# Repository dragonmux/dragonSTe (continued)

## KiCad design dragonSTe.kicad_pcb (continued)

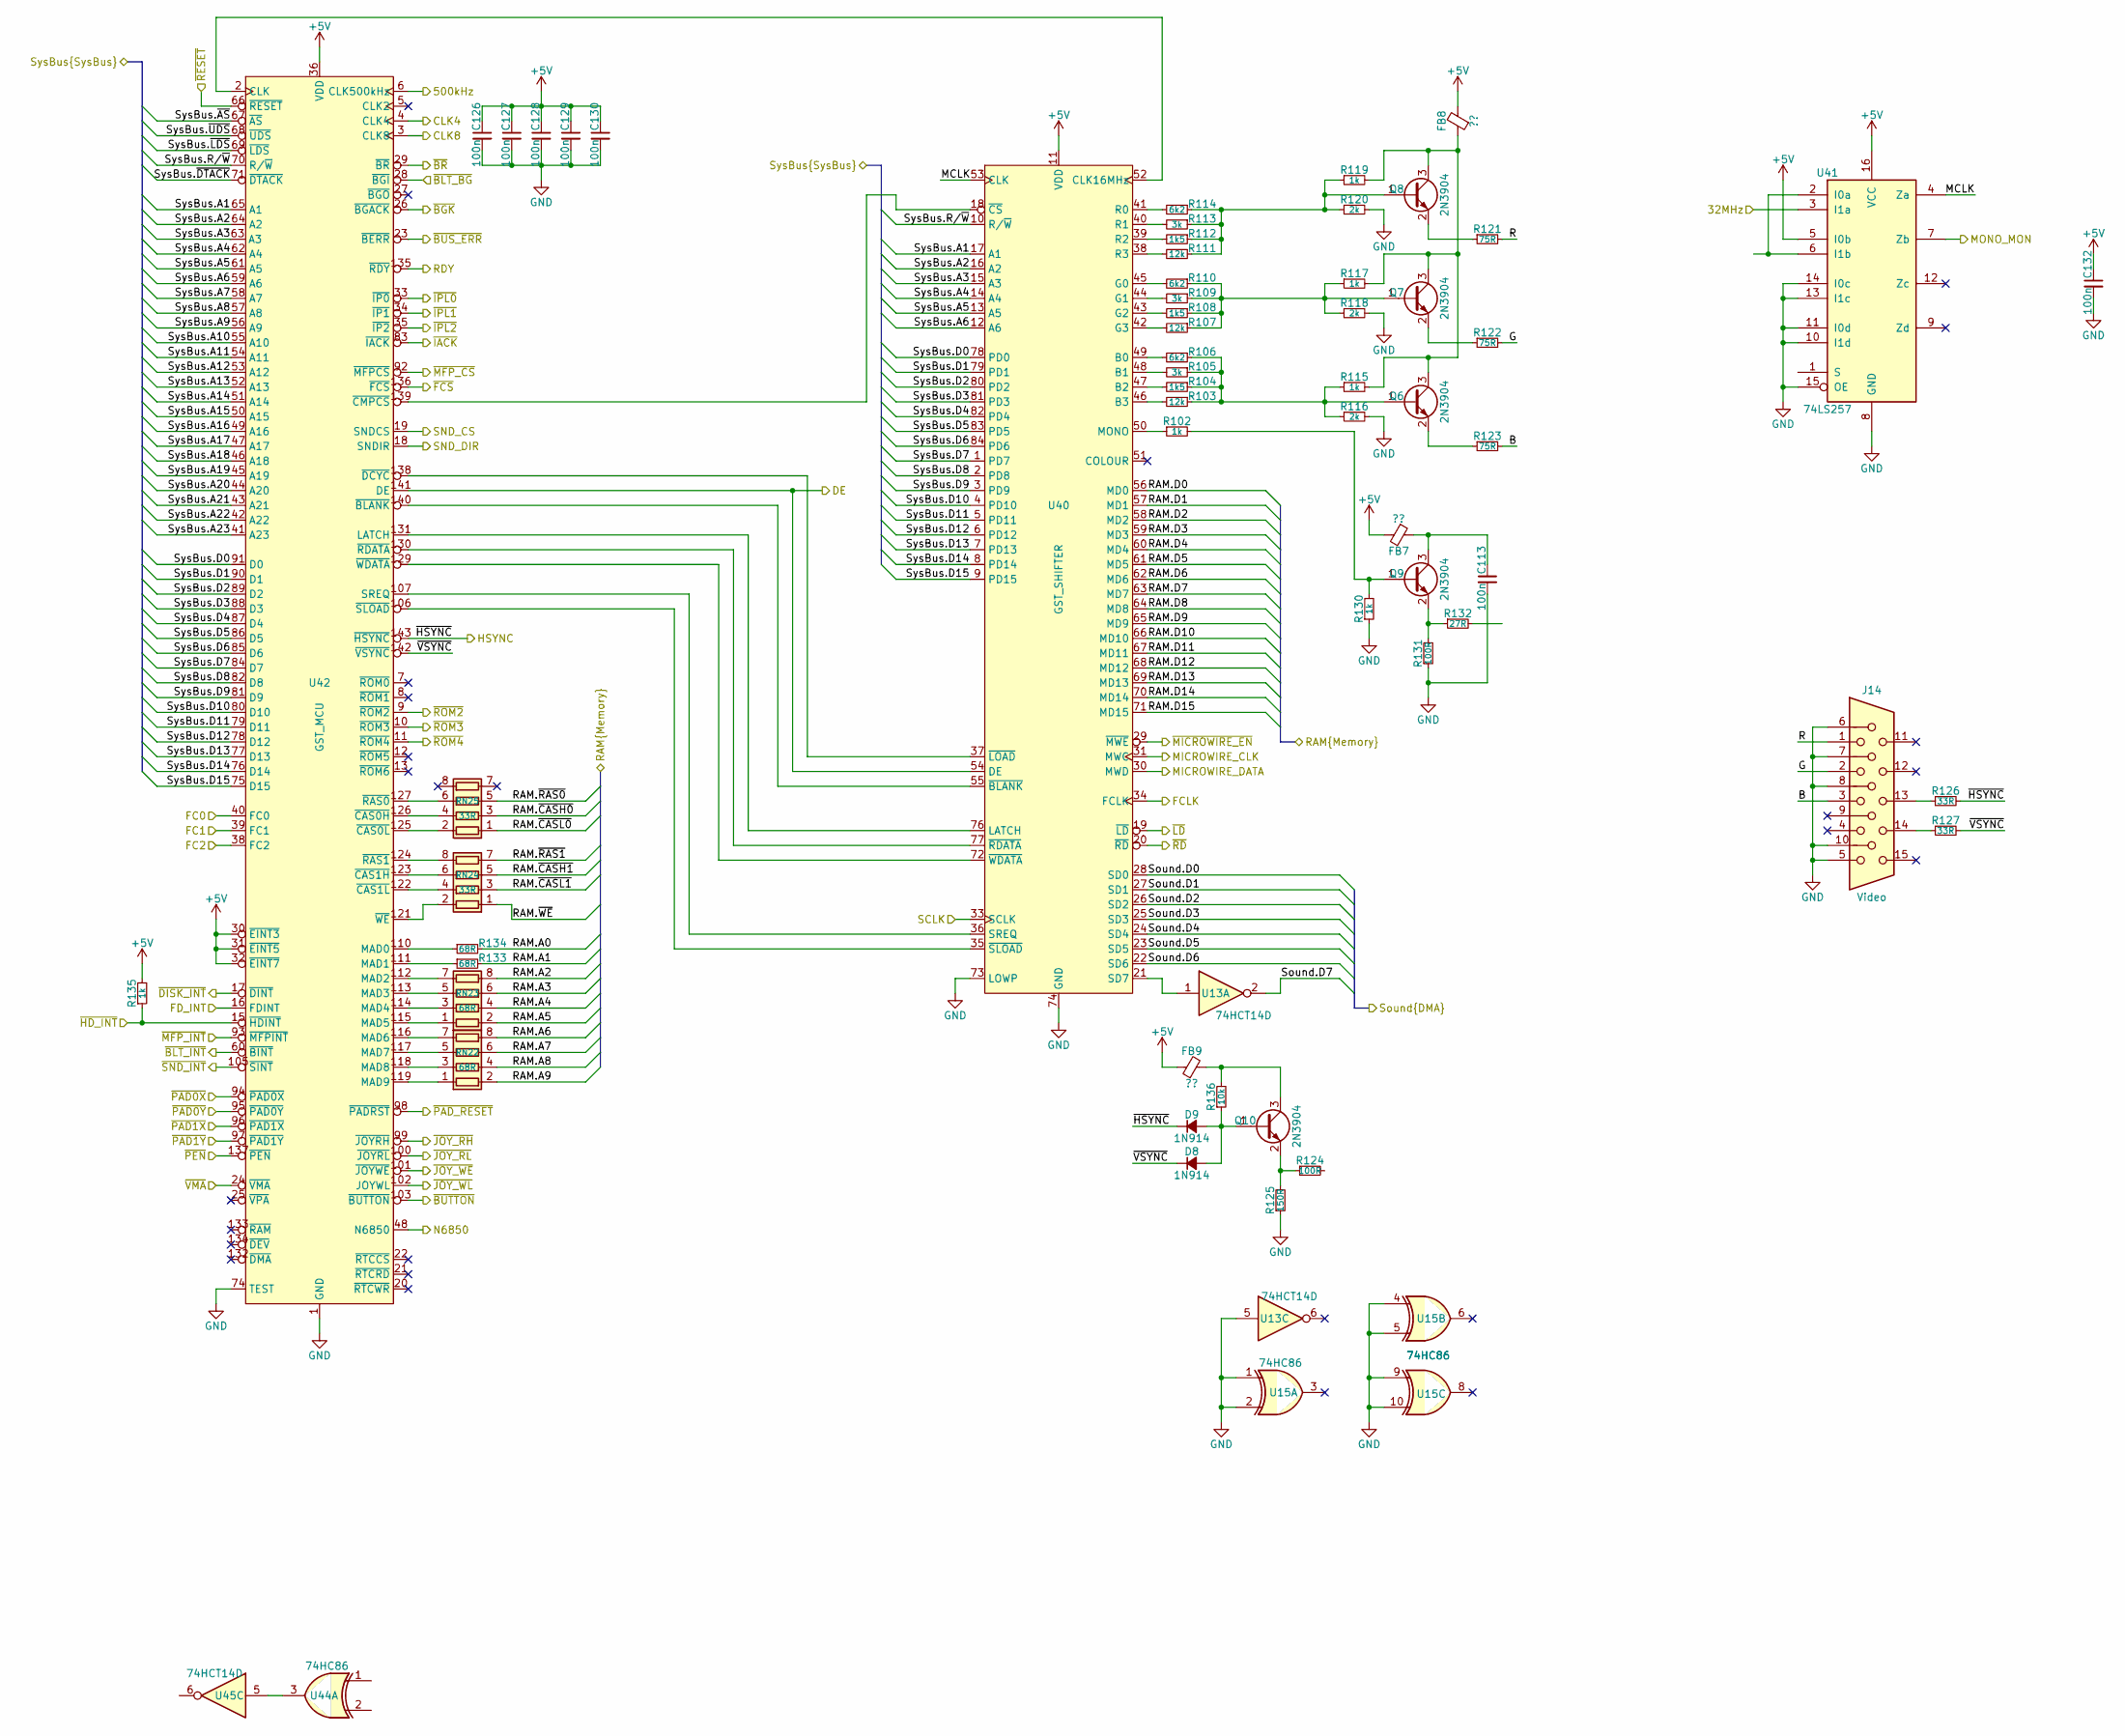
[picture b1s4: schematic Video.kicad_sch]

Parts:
C113, C126, C127, C128, C129, C130, C132: 100n; C0603
D8, D9: 1N914; D_SOD-323F; MPN 1N914BWS
FB7, FB8, FB9: ??
J14: Video; DSUB-15-HD_Socket_Horizontal_P2.29x2.54mm_EdgePinOffset8.35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
Q6, Q7, Q8, Q9, Q10: 2N3904; SOT-23; MPN MMBT3904,215
R102, R115, R117, R119, R130, R135: 1k; R0603
R103, R107, R111: 12k; R0603
R104, R108, R112: 1k5; R0603
R105, R109, R113: 3k; R0603
R106, R110, R114: 6k2; R0603
R116, R118, R120: 2k; R0603
R121, R122, R123: 75R; R0603
R124, R131: 100R; R0603
R125: 150R; R0603
R126, R127: 33R; R0603
R132: 27R; R0603
R133, R134: 68R; R0402
R136: 10k; R0603
RN22, RN23: 68R; R0402_Array_Convex_4
RN24, RN25: 33R; R0402_Array_Convex_4
U13, U45: 74HCT14D; SO-14_3.9x8.65mm_P1.27mm; MPN 74HCT14D,653
U15, U44: 74HC86; SO-14_3.9x8.65mm_P1.27mm; MPN 74HC86D,653
U40: GST_SHIFTER; PLCC-84_SMD-Socket
U41: 74LS257; TSSOP-16_4.4x5mm_P0.65mm; MPN 74HC257PW,118
U42: GST_MCU; LQFP-144_20x20mm_P0.5mm

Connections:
+5V: C126.1, C127.1, C128.1, C129.1, C130.1, C132.1, FB7.2, FB8.2, FB9.1, R135.2, U40.11 (VDD), U40.32 (VDD), U41.5 (I0b), U41.16 (VCC), U42.30 (~EINT3), U42.31 (~EINT5), U42.32 (~EINT7), U42.36 (VDD), U42.72 (VDD), U42.108 (VDD), U42.120 (VDD), U42.144 (VDD); also elsewhere on the board
/CPU+ROMs/32MHz: U41.3 (I1a); also elsewhere on the board
/CPU+ROMs/CLK8: U42.3 (CLK8); also elsewhere on the board
/CPU+ROMs/FC0: U42.40 (FC0); also elsewhere on the board
/CPU+ROMs/FC1: U42.39 (FC1); also elsewhere on the board
/CPU+ROMs/FC2: U42.38 (FC2); also elsewhere on the board
/CPU+ROMs/SysBus.A1: U40.17 (A1), U42.65 (A1); also elsewhere on the board
/CPU+ROMs/SysBus.A2: U40.16 (A2), U42.64 (A2); also elsewhere on the board
/CPU+ROMs/SysBus.A3: U40.15 (A3); also elsewhere on the board
/CPU+ROMs/SysBus.A4: U40.14 (A4), U42.62 (A4); also elsewhere on the board
/CPU+ROMs/SysBus.A5: U40.13 (A5), U42.61 (A5); also elsewhere on the board
/CPU+ROMs/SysBus.A6: U40.12 (A6), U42.59 (A6); also elsewhere on the board
/CPU+ROMs/SysBus.A7: U42.58 (A7); also elsewhere on the board
/CPU+ROMs/SysBus.A8: U42.57 (A8); also elsewhere on the board
/CPU+ROMs/SysBus.A9: U42.56 (A9); also elsewhere on the board
/CPU+ROMs/SysBus.A10: U42.55 (A10); also elsewhere on the board
/CPU+ROMs/SysBus.A11: U42.54 (A11); also elsewhere on the board
/CPU+ROMs/SysBus.A12: U42.53 (A12); also elsewhere on the board
/CPU+ROMs/SysBus.A13: U42.52 (A13); also elsewhere on the board
/CPU+ROMs/SysBus.A14: U42.51 (A14); also elsewhere on the board
/CPU+ROMs/SysBus.A15: U42.50 (A15); also elsewhere on the board
/CPU+ROMs/SysBus.A16: U42.49 (A16); also elsewhere on the board
/CPU+ROMs/SysBus.A17: U42.47 (A17); also elsewhere on the board
/CPU+ROMs/SysBus.A18: U42.46 (A18); also elsewhere on the board
/CPU+ROMs/SysBus.A19: U42.45 (A19); also elsewhere on the board
/CPU+ROMs/SysBus.A20: U42.44 (A20); also elsewhere on the board
/CPU+ROMs/SysBus.A21: U42.43 (A21); also elsewhere on the board
/CPU+ROMs/SysBus.A22: U42.42 (A22); also elsewhere on the board
/CPU+ROMs/SysBus.A23: U42.41 (A23); also elsewhere on the board
/CPU+ROMs/SysBus.D0: U40.78 (PD0), U42.91 (D0); also elsewhere on the board
/CPU+ROMs/SysBus.D1: U40.79 (PD1), U42.90 (D1); also elsewhere on the board
/CPU+ROMs/SysBus.D2: U40.80 (PD2), U42.89 (D2); also elsewhere on the board
/CPU+ROMs/SysBus.D3: U40.81 (PD3), U42.88 (D3); also elsewhere on the board
/CPU+ROMs/SysBus.D4: U40.82 (PD4), U42.87 (D4); also elsewhere on the board
/CPU+ROMs/SysBus.D5: U40.83 (PD5), U42.86 (D5); also elsewhere on the board
/CPU+ROMs/SysBus.D6: U40.84 (PD6), U42.85 (D6); also elsewhere on the board
/CPU+ROMs/SysBus.D7: U40.1 (PD7), U42.84 (D7); also elsewhere on the board
/CPU+ROMs/SysBus.D8: U40.2 (PD8), U42.82 (D8); also elsewhere on the board
/CPU+ROMs/SysBus.D9: U40.3 (PD9), U42.81 (D9); also elsewhere on the board
/CPU+ROMs/SysBus.D10: U40.4 (PD10), U42.80 (D10); also elsewhere on the board
/CPU+ROMs/SysBus.D11: U40.5 (PD11), U42.79 (D11); also elsewhere on the board
/CPU+ROMs/SysBus.D12: U40.6 (PD12), U42.78 (D12); also elsewhere on the board
/CPU+ROMs/SysBus.D13: U40.7 (PD13), U42.77 (D13); also elsewhere on the board
/CPU+ROMs/SysBus.D14: U40.8 (PD14), U42.76 (D14); also elsewhere on the board
/CPU+ROMs/SysBus.D15: U40.9 (PD15), U42.75 (D15); also elsewhere on the board
/CPU+ROMs/SysBus.R/~W: U40.10 (R/~W), U42.70 (R/~W); also elsewhere on the board
/CPU+ROMs/SysBus.~AS: U42.67 (~AS); also elsewhere on the board
/CPU+ROMs/SysBus.~DTACK: U42.71 (~DTACK); also elsewhere on the board
/CPU+ROMs/SysBus.~LDS: U42.69 (~LDS); also elsewhere on the board
/CPU+ROMs/SysBus.~UDS: U42.68 (~UDS); also elsewhere on the board
/CPU+ROMs/~BGK: U42.26 (~BGACK); also elsewhere on the board
/CPU+ROMs/~BLT_BG: U42.28 (~BGI); also elsewhere on the board
/CPU+ROMs/~BLT_INT: U42.60 (~BINT); also elsewhere on the board
/CPU+ROMs/~BR: U42.29 (~BR); also elsewhere on the board
/CPU+ROMs/~BUS_ERR: U42.23 (~BERR); also elsewhere on the board
/CPU+ROMs/~IPL0: U42.33 (~IP0); also elsewhere on the board
/CPU+ROMs/~IPL1: U42.34 (~IP1); also elsewhere on the board
/CPU+ROMs/~IPL2: U42.35 (~IP2); also elsewhere on the board
/CPU+ROMs/~RESET: U42.66 (~RESET); also elsewhere on the board
/CPU+ROMs/~ROM2: U42.9 (~ROM2); also elsewhere on the board
/CPU+ROMs/~ROM3: U42.10 (~ROM3)
/CPU+ROMs/~ROM4: U42.11 (~ROM4)
/DAC + Joysticks/MICROWIRE_CLK: U40.31 (MWC); also elsewhere on the board
/DAC + Joysticks/MICROWIRE_DATA: U40.30 (MWD); also elsewhere on the board
/DAC + Joysticks/Sound.D0: U40.28 (SD0); also elsewhere on the board
/DAC + Joysticks/Sound.D1: U40.27 (SD1); also elsewhere on the board
/DAC + Joysticks/Sound.D2: U40.26 (SD2); also elsewhere on the board
/DAC + Joysticks/Sound.D3: U40.25 (SD3); also elsewhere on the board
/DAC + Joysticks/Sound.D4: U40.24 (SD4); also elsewhere on the board
/DAC + Joysticks/Sound.D5: U40.23 (SD5); also elsewhere on the board
/DAC + Joysticks/Sound.D6: U40.22 (SD6); also elsewhere on the board
/DAC + Joysticks/Sound.D7: U13.2; also elsewhere on the board
/DAC + Joysticks/~BUTTON: U42.103 (~BUTTON); also elsewhere on the board
/DAC + Joysticks/~JOY_RH: U42.99 (~JOYRH); also elsewhere on the board
/DAC + Joysticks/~JOY_RL: U42.100 (~JOYRL); also elsewhere on the board
/DAC + Joysticks/~JOY_WE: U42.101 (~JOYWE); also elsewhere on the board
/DAC + Joysticks/~JOY_WL: U42.102 (JOYWL); also elsewhere on the board
/DAC + Joysticks/~LD: U40.19 (~LD); also elsewhere on the board
/DAC + Joysticks/~MICROWIRE_EN: U40.29 (~MWE); also elsewhere on the board
/DAC + Joysticks/~PAD0X: U42.94 (~PAD0X)
/DAC + Joysticks/~PAD0Y: U42.95 (~PAD0Y)
/DAC + Joysticks/~PAD1X: U42.96 (~PAD1X)
/DAC + Joysticks/~PAD1Y: U42.97 (~PAD1Y)
/DAC + Joysticks/~PAD_RESET: U42.98 (~PADRST)
/DAC + Joysticks/~PEN: U42.137 (~PEN); also elsewhere on the board
/DAC + Joysticks/~RD: U40.20 (~RD); also elsewhere on the board
/Disk & Floppy/FD_INT: U42.16 (FDINT); also elsewhere on the board
/Disk & Floppy/RDY: U42.135 (~RDY); also elsewhere on the board
/Disk & Floppy/SCLK: U40.33 (SCLK); also elsewhere on the board
/Disk & Floppy/~FCS: U42.136 (~FCS); also elsewhere on the board
/Disk & Floppy/~HD_INT: R135.1, U42.15 (~HDINT)
/IO Interfaces/500kHz: U42.6 (CLK500kHz); also elsewhere on the board
/IO Interfaces/CLK4: U42.4 (CLK4); also elsewhere on the board
/IO Interfaces/DE: U40.54 (DE), U42.141 (DE); also elsewhere on the board
/IO Interfaces/MONO_MON: U41.7 (Zb); also elsewhere on the board
/IO Interfaces/N6850: U42.48 (N6850); also elsewhere on the board
/IO Interfaces/SND_CS: U42.19 (SNDCS); also elsewhere on the board
/IO Interfaces/SND_DIR: U42.18 (SNDIR); also elsewhere on the board
/IO Interfaces/~DISK_INT: U42.17 (~DINT); also elsewhere on the board
/IO Interfaces/~IACK: U42.83 (~IACK); also elsewhere on the board
/IO Interfaces/~MFP_CS: U42.92 (~MFPCS); also elsewhere on the board
/IO Interfaces/~MFP_INT: U42.93 (~MFPINT); also elsewhere on the board
/IO Interfaces/~SND_INT: U42.105 (~SINT); also elsewhere on the board
/RAM/RAM.A0: R134.2
/RAM/RAM.A1: R133.2
/RAM/RAM.A2: RN23.8 (R1.2)
/RAM/RAM.A3: RN23.6 (R3.2)
/RAM/RAM.A4: RN23.4 (R4.1)
/RAM/RAM.A5: RN23.2 (R2.1)
/RAM/RAM.A6: RN22.8 (R1.2)
/RAM/RAM.A7: RN22.6 (R3.2)
/RAM/RAM.A8: RN22.4 (R4.1)
/RAM/RAM.A9: RN22.2 (R2.1)
/RAM/RAM.D0: U40.56 (MD0)
/RAM/RAM.D1: U40.57 (MD1)
/RAM/RAM.D2: U40.58 (MD2)
/RAM/RAM.D3: U40.59 (MD3)
/RAM/RAM.D4: U40.60 (MD4)
/RAM/RAM.D5: U40.61 (MD5)
/RAM/RAM.D6: U40.62 (MD6)
/RAM/RAM.D7: U40.63 (MD7)
/RAM/RAM.D8: U40.64 (MD8)
/RAM/RAM.D9: U40.65 (MD9)
/RAM/RAM.D10: U40.66 (MD10)
/RAM/RAM.D11: U40.67 (MD11)
/RAM/RAM.D12: U40.68 (MD12)
/RAM/RAM.D13: U40.69 (MD13)
/RAM/RAM.D14: U40.70 (MD14)
/RAM/RAM.D15: U40.71 (MD15)
/RAM/RAM.~CASH0: RN25.3 (R3.1)
/RAM/RAM.~CASH1: RN24.5 (R4.2)
/RAM/RAM.~CASL0: RN25.1 (R1.1)
/RAM/RAM.~CASL1: RN24.3 (R3.1)
/RAM/RAM.~RAS0: RN25.5 (R4.2)
/RAM/RAM.~RAS1: RN24.7 (R2.2)
/RAM/RAM.~WE: RN24.1 (R1.1)
/Video/B: J14.3, R123.2
/Video/FCLK: U40.34 (FCLK)
/Video/G: J14.2, R122.2
/Video/MCLK: U40.53 (CLK), U41.4 (Za)
/Video/R: J14.1, R121.2
/Video/~HSYNC: D9.1 (K), R126.2, U42.143 (~HSYNC)
/Video/~VMA: U42.24 (~VMA)
/Video/~VSYNC: D8.1 (K), R127.2, U42.142 (~VSYNC)
GND: C113.2, C126.2, C127.2, C128.2, C129.2, C130.2, C132.2, J14.5, J14.6, J14.7, J14.8, J14.10, R116.2, R118.2, R120.2, R125.1, R130.1, R131.1, U13.5, U15.1, U15.2, U15.4, U15.5, U15.9, U15.10, U40.73 (LOWP), U40.74 (GND), U40.75 (GND), U41.8 (GND), U41.10 (I1d), U41.11 (I0d), U41.13 (I1c), U41.14 (I0c), U41.15 (OE), U42.1 (GND), U42.37 (GND), U42.73 (GND), U42.74 (TEST), U42.109 (GND), U42.128 (GND); also elsewhere on the board
unnamed: C113.1, FB7.1, Q9.3 (C)
unnamed: D8.2 (A), D9.2 (A), Q10.1 (B), R136.1
unnamed: FB9.2, Q10.3 (C), R136.2
unnamed: J14.13, R126.1
unnamed: J14.14, R127.1
unnamed: Q6.2 (E), R123.1
unnamed: Q6.1 (B), R103.1, R104.1, R105.1, R106.1, R115.1, R116.1
unnamed: Q7.1 (B), R107.1, R108.1, R109.1, R110.1, R117.1, R118.1
unnamed: Q7.2 (E), R122.1
unnamed: Q8.1 (B), R111.1, R112.1, R113.1, R114.1, R119.1, R120.1
unnamed: FB8.1, Q6.3 (C), Q7.3 (C), Q8.3 (C), R115.2, R117.2, R119.2
unnamed: Q8.2 (E), R121.1
unnamed: Q9.2 (E), R131.2, R132.1
unnamed: Q9.1 (B), R102.2, R130.2
unnamed: Q10.2 (E), R124.1, R125.2
unnamed: RN22.1 (R1.1), U42.119 (MAD9)
unnamed: RN22.7 (R2.2), U42.116 (MAD6)
unnamed: RN22.3 (R3.1), U42.118 (MAD8)
unnamed: RN22.5 (R4.2), U42.117 (MAD7)
unnamed: RN23.1 (R1.1), U42.115 (MAD5)
unnamed: RN23.7 (R2.2), U42.112 (MAD2)
unnamed: RN23.3 (R3.1), U42.114 (MAD4)
unnamed: RN23.5 (R4.2), U42.113 (MAD3)
unnamed: RN24.8 (R1.2), U42.124 (~RAS1)
unnamed: RN24.2 (R2.1), U42.121 (~WE)
unnamed: RN24.6 (R3.2), U42.123 (~CAS1H)
unnamed: RN24.4 (R4.1), U42.122 (~CAS1L)
unnamed: RN25.2 (R2.1), U42.125 (~CAS0L)
unnamed: RN25.6 (R3.2), U42.127 (~RAS0)
unnamed: RN25.4 (R4.1), U42.126 (~CAS0H)
unnamed: R106.2, U40.49 (B0)
unnamed: R105.2, U40.48 (B1)
unnamed: R104.2, U40.47 (B2)
unnamed: R103.2, U40.46 (B3)
unnamed: U40.52 (CLK16MHz), U42.2 (CLK)
unnamed: R110.2, U40.45 (G0)
unnamed: R109.2, U40.44 (G1)
unnamed: R108.2, U40.43 (G2)
unnamed: R107.2, U40.42 (G3)
unnamed: U40.76 (LATCH), U42.131 (LATCH)
unnamed: R102.1, U40.50 (MONO)
unnamed: R114.2, U40.41 (R0)
unnamed: R113.2, U40.40 (R1)
unnamed: R112.2, U40.39 (R2)
unnamed: R111.2, U40.38 (R3)
unnamed: U13.1, U40.21 (SD7)
unnamed: U40.36 (SREQ), U42.107 (SREQ)
unnamed: U40.55 (~BLANK), U42.140 (~BLANK)
unnamed: U40.18 (~CS), U42.139 (~CMPCS)
unnamed: U40.37 (~LOAD), U42.138 (~DCYC)
unnamed: U40.77 (~RDATA), U42.130 (~RDATA)
unnamed: U40.35 (~SLOAD), U42.106 (~SLOAD)
unnamed: U40.72 (~WDATA), U42.129 (~WDATA)
unnamed: U41.2 (I0a), U41.6 (I1b)
unnamed: R134.1, U42.110 (MAD0)
unnamed: R133.1, U42.111 (MAD1)
unnamed: U44.3, U45.5

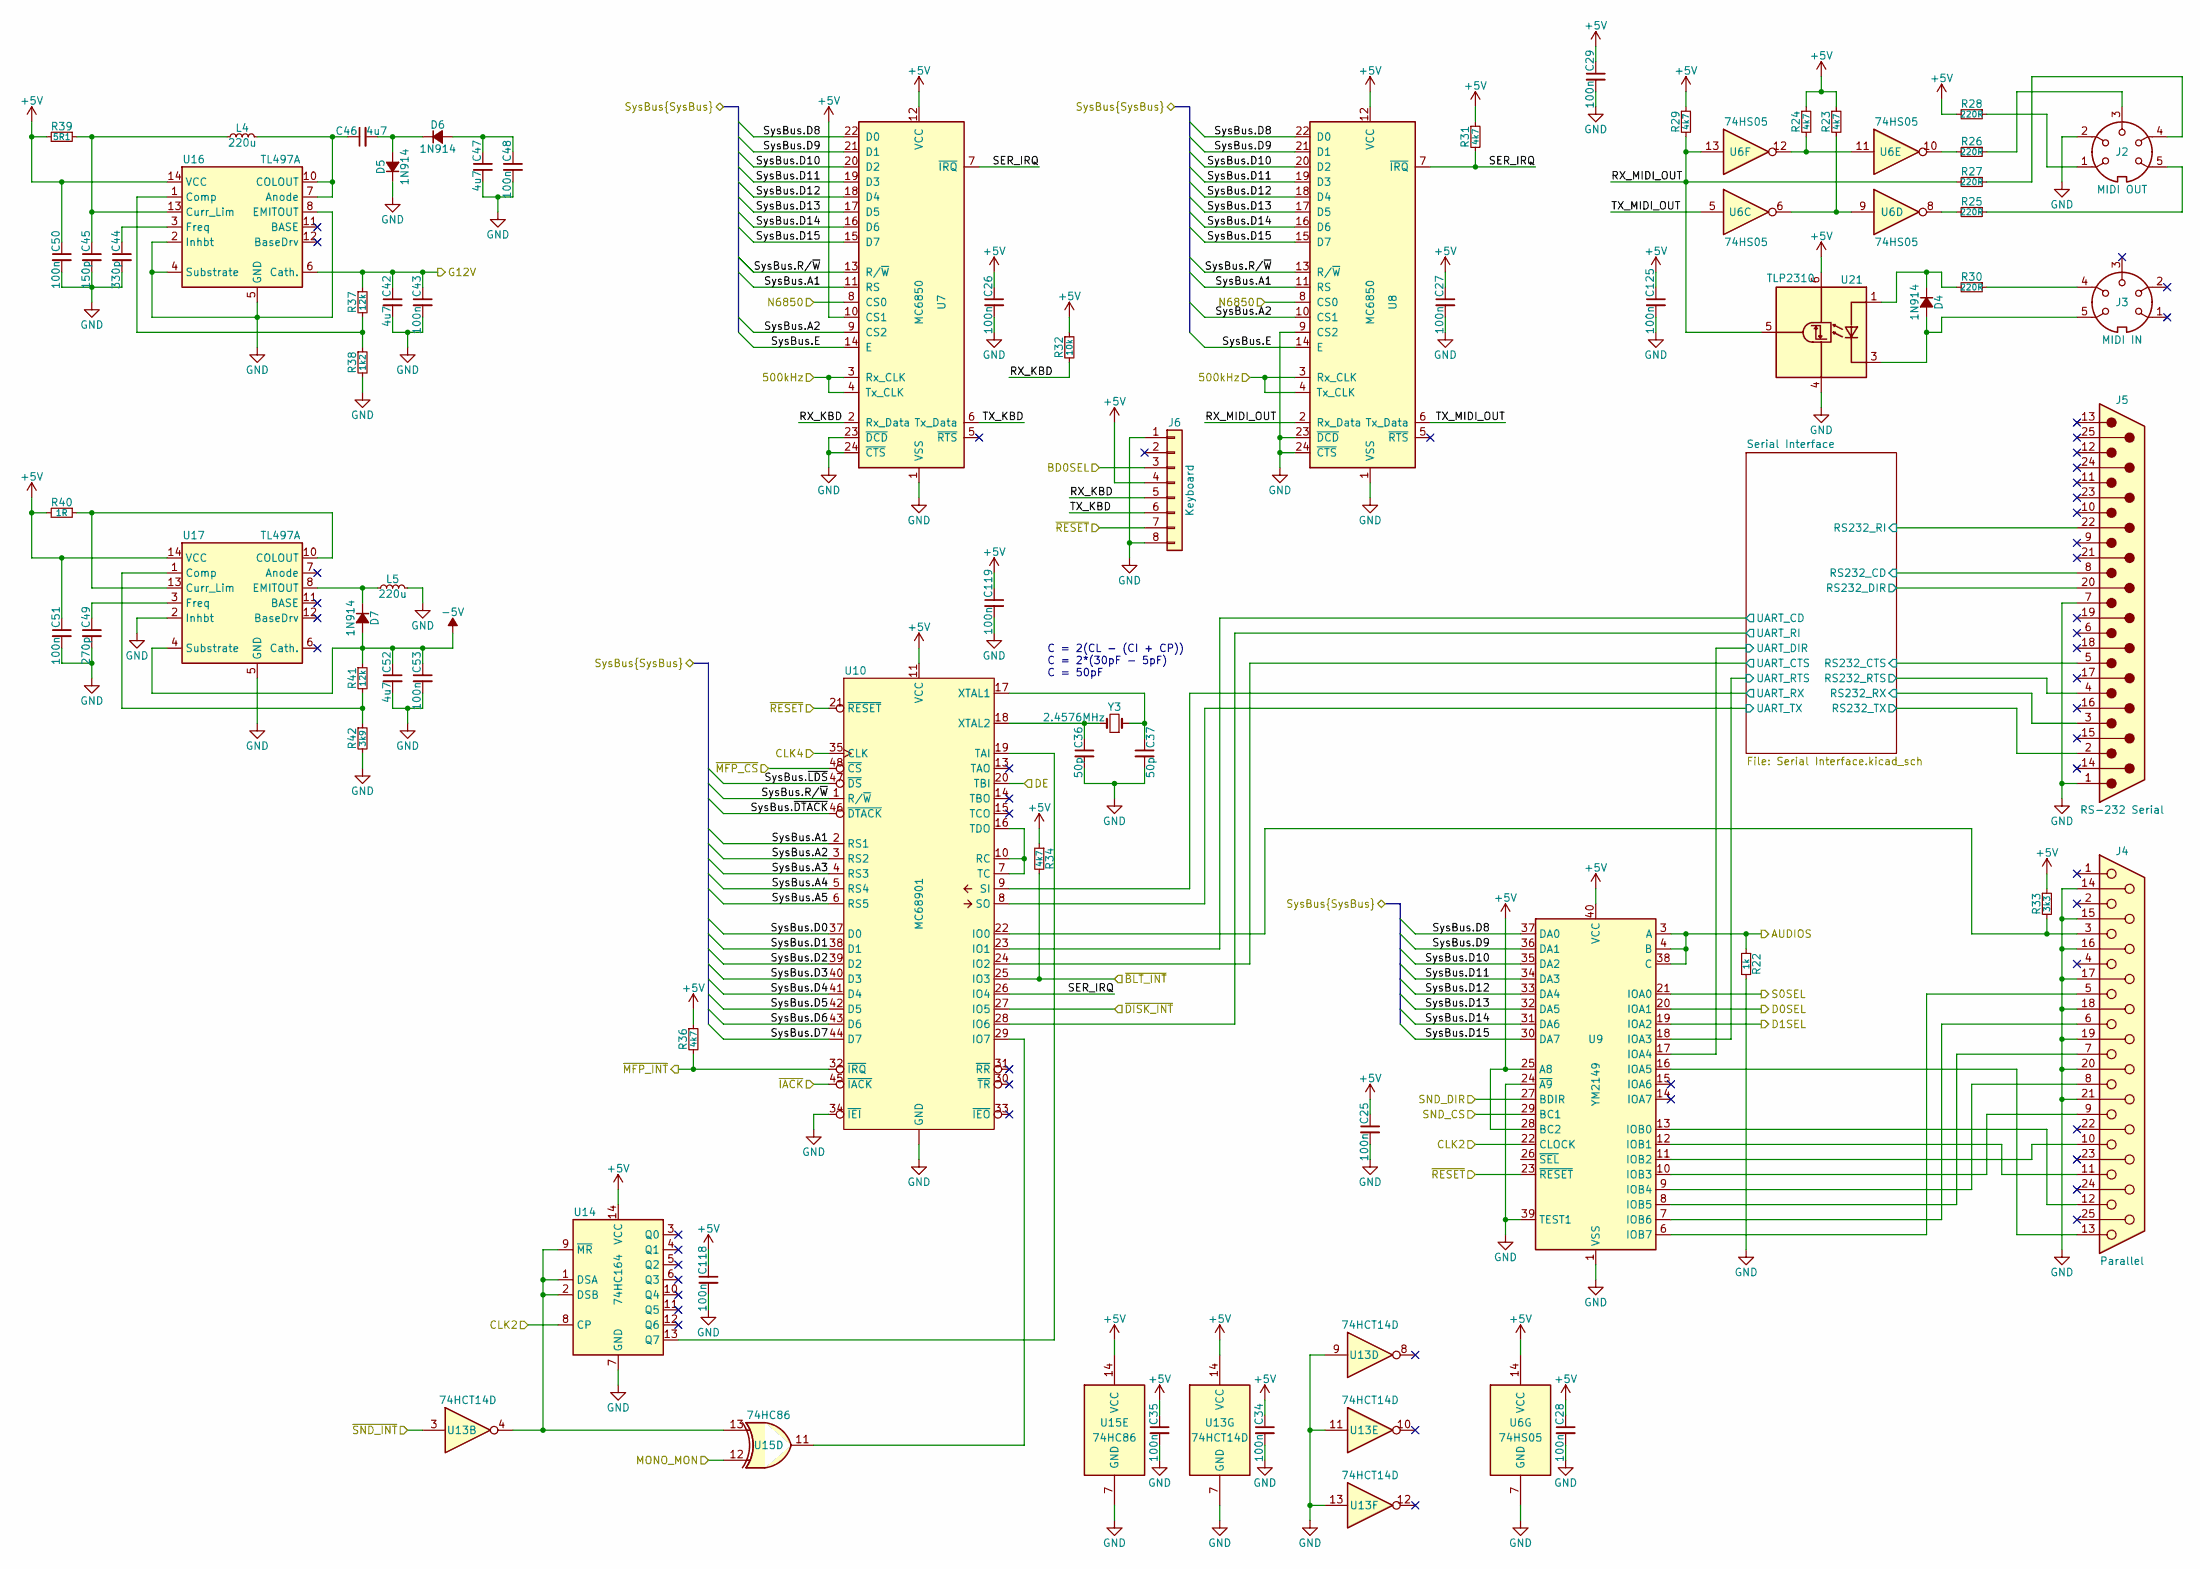
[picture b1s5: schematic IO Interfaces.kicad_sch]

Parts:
C25, C26, C27, C28, C29, C34, C35, C43, C48, C50, C51, C53, C118, C119, C125: 100n; C0603
C36, C37: 50p; C0603
C42, C46, C47, C52: 4u7; C0603
C44: 330p; C0603
C45: 150p; C0603
C49: 270p; C0603
D4, D5, D6, D7: 1N914; D_SOD-323F; MPN 1N914BWS
J2: MIDI OUT; 0105_05
J3: MIDI IN; 0105_05
J4: Parallel; DSUB-25_Socket_Horizontal_P2.77x2.84mm_EdgePinOffset7.70mm_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; MPN 5504F1-25S-02-03-F1
J5: RS-232 Serial; DSUB-25_Pins_Horizontal_P2.77x2.84mm_EdgePinOffset7.70mm_Ho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; MPN 5504F1-25P-02-03-F1
J6: Keyboard; PinHeader_1x08_P2.54mm_Vertical
L4, L5: 220u
R22: 1k; R0603
R23, R24, R29, R31, R34, R36: 4k7; R0603
R25, R26, R27, R28, R30: 220R; R0603
R32: 10k; R0603
R33: 3k3; R0603
R37, R41: 12k; R0603
R38: 1k2; R0603
R39: 5R1; R0603
R40: 1R; R0603
R42: 3k9; R0603
U6: 74HS05; SO-14_3.9x8.65mm_P1.27mm; MPN SN74HC05DR
U7, U8: MC6850; DIP-24_W15.24mm_Socket; MPN SPC15503
U9: YM2149; DIP-40_W15.24mm_Socket
U10: MC68901; DIP-48_W15.24mm_Socket; MPN SPC15558
U13: 74HCT14D; SO-14_3.9x8.65mm_P1.27mm; MPN 74HCT14D,653
U14: 74HC164; SO-14_3.9x8.65mm_P1.27mm; MPN 74HC164D,653
U15: 74HC86; SO-14_3.9x8.65mm_P1.27mm; MPN 74HC86D,653
U16, U17: TL497A
U21: TLP2310; SO-5-6_4.55x3.7mm_P1.27mm; MPN TLP2363(TPL,E(T
Y3: 2.4576MHz; Crystal_HC49-U_Vertical; MPN LFXTAL003044

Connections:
+5V: C25.1, C26.1, C27.1, C28.1, C29.1, C34.1, C35.1, C50.1, C51.1, C118.1, C119.1, C125.1, J6.4, R23.1, R24.1, R28.2, R29.1, R31.1, R32.1, R33.1, R34.1, R36.1, R39.2, R40.2, U6.14 (VCC), U7.10 (CS1), U7.12 (VCC), U8.12 (VCC), U9.25 (A8), U9.28 (BC2), U9.40 (VCC), U10.11 (VCC), U13.14 (VCC), U14.14 (VCC), U15.14 (VCC), U16.14 (VCC), U17.14 (VCC), U21.6 (VDD); also elsewhere on the board
-5V: C52.1, C53.1, D7.2 (A), R41.1, U17.4 (Substrate); also elsewhere on the board
/CPU+ROMs/SysBus.A1: U7.11 (RS), U8.11 (RS), U10.2 (RS1); also elsewhere on the board
/CPU+ROMs/SysBus.A2: U7.9 (CS2), U8.10 (CS1), U10.3 (RS2); also elsewhere on the board
/CPU+ROMs/SysBus.A3: U10.4 (RS3); also elsewhere on the board
/CPU+ROMs/SysBus.A4: U10.5 (RS4); also elsewhere on the board
/CPU+ROMs/SysBus.A5: U10.6 (RS5); also elsewhere on the board
/CPU+ROMs/SysBus.D0: U10.37 (D0); also elsewhere on the board
/CPU+ROMs/SysBus.D1: U10.38 (D1); also elsewhere on the board
/CPU+ROMs/SysBus.D2: U10.39 (D2); also elsewhere on the board
/CPU+ROMs/SysBus.D3: U10.40 (D3); also elsewhere on the board
/CPU+ROMs/SysBus.D4: U10.41 (D4); also elsewhere on the board
/CPU+ROMs/SysBus.D5: U10.42 (D5); also elsewhere on the board
/CPU+ROMs/SysBus.D6: U10.43 (D6); also elsewhere on the board
/CPU+ROMs/SysBus.D7: U10.44 (D7); also elsewhere on the board
/CPU+ROMs/SysBus.D8: U7.22 (D0), U8.22 (D0), U9.37 (DA0); also elsewhere on the board
/CPU+ROMs/SysBus.D9: U7.21 (D1), U8.21 (D1), U9.36 (DA1); also elsewhere on the board
/CPU+ROMs/SysBus.D10: U7.20 (D2), U8.20 (D2), U9.35 (DA2); also elsewhere on the board
/CPU+ROMs/SysBus.D11: U7.19 (D3), U8.19 (D3), U9.34 (DA3); also elsewhere on the board
/CPU+ROMs/SysBus.D12: U7.18 (D4), U8.18 (D4), U9.33 (DA4); also elsewhere on the board
/CPU+ROMs/SysBus.D13: U7.17 (D5), U8.17 (D5), U9.32 (DA5); also elsewhere on the board
/CPU+ROMs/SysBus.D14: U7.16 (D6), U8.16 (D6), U9.31 (DA6); also elsewhere on the board
/CPU+ROMs/SysBus.D15: U7.15 (D7), U8.15 (D7), U9.30 (DA7); also elsewhere on the board
/CPU+ROMs/SysBus.E: U7.14 (E), U8.14 (E); also elsewhere on the board
/CPU+ROMs/SysBus.R/~W: U7.13 (R/~W), U8.13 (R/~W), U10.1 (R/~W); also elsewhere on the board
/CPU+ROMs/SysBus.~DTACK: U10.46 (~DTACK); also elsewhere on the board
/CPU+ROMs/SysBus.~LDS: U10.47 (~DS); also elsewhere on the board
/CPU+ROMs/~BLT_INT: R34.2, U10.25 (IO3); also elsewhere on the board
/CPU+ROMs/~RESET: J6.7, U9.23 (~RESET), U10.21 (~RESET); also elsewhere on the board
/DAC + Joysticks/AUDIOS: R22.1, U9.3 (A), U9.4 (B), U9.38 (C); also elsewhere on the board
/Disk & Floppy/BD0SEL: J6.3; also elsewhere on the board
/Disk & Floppy/CLK2: U9.22 (CLOCK), U14.8 (CP); also elsewhere on the board
/Disk & Floppy/D0SEL: U9.20 (IOA1); also elsewhere on the board
/Disk & Floppy/D1SEL: U9.19 (IOA2); also elsewhere on the board
/Disk & Floppy/S0SEL: U9.21 (IOA0); also elsewhere on the board
/IO Interfaces/500kHz: U7.3 (Rx_CLK), U7.4 (Tx_CLK), U8.3 (Rx_CLK), U8.4 (Tx_CLK); also elsewhere on the board
/IO Interfaces/CLK4: U10.35 (CLK); also elsewhere on the board
/IO Interfaces/DE: U10.20 (TBI); also elsewhere on the board
/IO Interfaces/G12V: C42.1, C43.1, R37.1, U16.6 (Cath.)
/IO Interfaces/MONO_MON: U15.12; also elsewhere on the board
/IO Interfaces/N6850: U7.8 (CS0), U8.8 (CS0); also elsewhere on the board
/IO Interfaces/RX_KBD: J6.5, R32.2, U7.2 (Rx_Data)
/IO Interfaces/RX_MIDI_OUT: R27.2, R29.2, U6.13, U8.2 (Rx_Data), U21.5 (VO)
/IO Interfaces/SER_IRQ: R31.2, U7.7 (~IRQ), U8.7 (~IRQ), U10.26 (IO4)
/IO Interfaces/SND_CS: U9.29 (BC1); also elsewhere on the board
/IO Interfaces/SND_DIR: U9.27 (BDIR); also elsewhere on the board
/IO Interfaces/Serial Interface/RS232_CD: J5.8; also elsewhere on the board
/IO Interfaces/Serial Interface/RS232_CTS: J5.5; also elsewhere on the board
/IO Interfaces/Serial Interface/RS232_DIR: J5.20; also elsewhere on the board
/IO Interfaces/Serial Interface/RS232_RI: J5.22; also elsewhere on the board
/IO Interfaces/Serial Interface/RS232_RTS: J5.4; also elsewhere on the board
/IO Interfaces/Serial Interface/RS232_RX: J5.3; also elsewhere on the board
/IO Interfaces/Serial Interface/RS232_TX: J5.2; also elsewhere on the board
/IO Interfaces/Serial Interface/UART_CD: U10.23 (IO1); also elsewhere on the board
/IO Interfaces/Serial Interface/UART_CTS: U10.24 (IO2); also elsewhere on the board
/IO Interfaces/Serial Interface/UART_DIR: U9.17 (IOA4); also elsewhere on the board
/IO Interfaces/Serial Interface/UART_RI: U10.28 (IO6); also elsewhere on the board
/IO Interfaces/Serial Interface/UART_RTS: U9.18 (IOA3); also elsewhere on the board
/IO Interfaces/Serial Interface/UART_RX: U10.9 (SI); also elsewhere on the board
/IO Interfaces/Serial Interface/UART_TX: U10.8 (SO); also elsewhere on the board
/IO Interfaces/TX_KBD: J6.6, U7.6 (Tx_Data)
/IO Interfaces/TX_MIDI_OUT: U6.5, U8.6 (Tx_Data)
/IO Interfaces/~DISK_INT: U10.27 (IO5); also elsewhere on the board
/IO Interfaces/~IACK: U10.45 (~IACK); also elsewhere on the board
/IO Interfaces/~MFP_CS: U10.48 (~CS); also elsewhere on the board
/IO Interfaces/~MFP_INT: R36.2, U10.32 (~IRQ); also elsewhere on the board
/IO Interfaces/~SND_INT: U13.3; also elsewhere on the board
GND: C25.2, C26.2, C27.2, C28.2, C29.2, C34.2, C35.2, C36.2, C37.2, C42.2, C43.2, C44.2, C45.2, C47.2, C48.2, C49.2, C50.2, C51.2, C52.2, C53.2, C118.2, C119.2, C125.2, D5.1 (K), J2.2, J4.14, J4.15, J4.16, J4.17, J4.18, J4.19, J4.20, J4.21, J5.1, J5.7, J6.1, J6.8, L5.2, R22.2, R38.2, R42.2, U6.7 (GND), U7.1 (VSS), U7.23 (~DCD), U7.24 (~CTS), U8.1 (VSS), U8.9 (CS2), U8.23 (~DCD), U8.24 (~CTS), U9.1 (VSS), U9.24 (~A9), U9.39 (TEST1), U10. (GND), U10.34 (~IEI), U13.7 (GND), U13.9, U13.11, U13.13, U14.7 (GND), U15.7 (GND), U16.2 (Inhbt), U16.4 (Substrate), U16.5 (GND), U16.8 (EMITOUT), U17.2 (Inhbt), U17.5 (GND), U21.4 (GND); also elsewhere on the board
unnamed: D4.2 (A), J3.5, U21.3 (K)
unnamed: D4.1 (K), R30.2, U21.1 (A)
unnamed: C46.2, D5.2 (A), D6.1 (K)
unnamed: C47.1, C48.1, D6.2 (A)
unnamed: D7.1 (K), L5.1, U17.8 (EMITOUT)
unnamed: J2.1, R28.1
unnamed: J2.3, R26.1
unnamed: J2.4, R27.1
unnamed: J2.5, R25.1
unnamed: J3.4, R30.1
unnamed: R23.2, U6.6, U6.9
unnamed: R24.2, U6.11, U6.12
unnamed: R25.2, U6.8
unnamed: R26.2, U6.10
unnamed: J4.13, U9.16 (IOA5)
unnamed: J4.12, U9.13 (IOB0)
unnamed: J4.11, U9.12 (IOB1)
unnamed: J4.10, U9.11 (IOB2)
unnamed: J4.9, U9.10 (IOB3)
unnamed: J4.8, U9.9 (IOB4)
unnamed: J4.7, U9.8 (IOB5)
unnamed: J4.6, U9.7 (IOB6)
unnamed: J4.5, U9.6 (IOB7)
unnamed: J4.3, R33.2, U10.22 (IO0)
unnamed: U10.29 (IO7), U15.11
unnamed: U10.7 (TC), U10.10 (RC), U10.16 (TDO)
unnamed: U10.19 (TAI), U14.13 (Q7)
unnamed: C37.1, U10.17 (XTAL1), Y3.1
unnamed: C36.1, U10.18 (XTAL2), Y3.2
unnamed: U13.4, U14.1 (DSA), U14.2 (DSB), U14.9 (~MR), U15.13
unnamed: C46.1, L4.2, U16.7 (Anode), U16.10 (COLOUT)
unnamed: R37.2, R38.1, U16.1 (Comp)
unnamed: C45.1, L4.1, R39.1, U16.13 (Curr_Lim)
unnamed: C44.1, U16.3 (Freq)
unnamed: R40.1, U17.10 (COLOUT), U17.13 (Curr_Lim)
unnamed: R41.2, R42.1, U17.1 (Comp)
unnamed: C49.1, U17.3 (Freq)

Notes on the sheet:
C = 2(CL - (CI + CP)) C = 2*(30pF - 5pF) C = 50pF
